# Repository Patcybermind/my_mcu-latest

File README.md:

# simple and cheap atmega 328 board
for simple projects where you dont need a usb port and just want the bare minimum

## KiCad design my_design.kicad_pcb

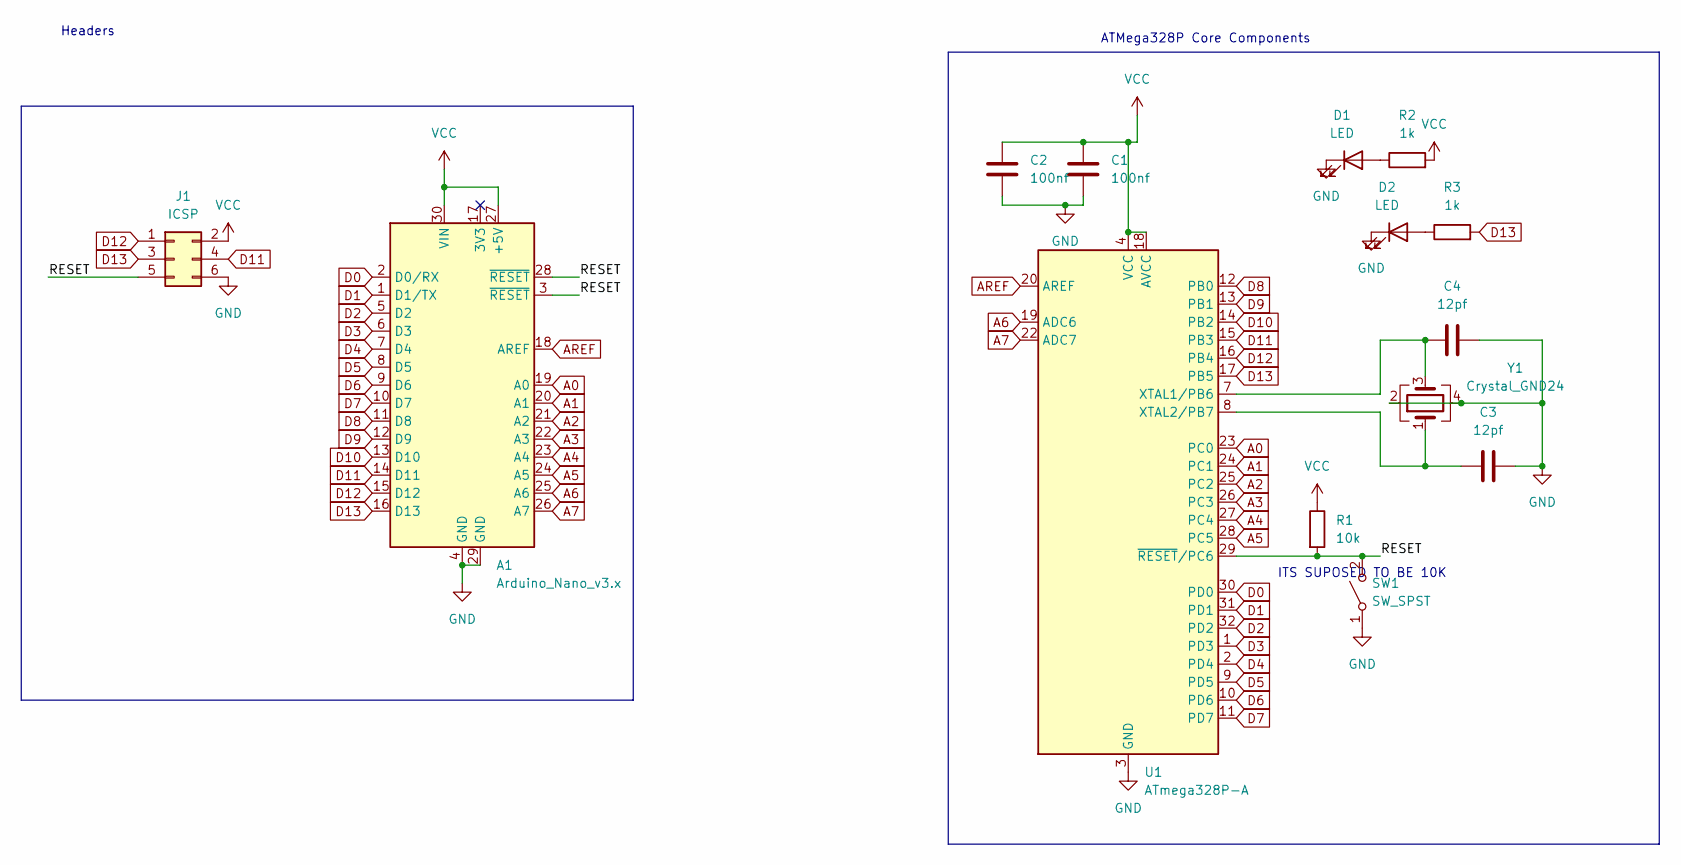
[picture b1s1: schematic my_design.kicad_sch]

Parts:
A1: Arduino_Nano_v3.x; Arduino_Nano_WithMountingHoles
C1, C2: 100nf; C_0805_2012Metric_Pad1.18x1.45mm_HandSolder; LCSC C49678
C3, C4: 12pf; C_0805_2012Metric_Pad1.18x1.45mm_HandSolder; LCSC C1792
D1, D2: LED; LED_0805_2012Metric_Pad1.15x1.40mm_HandSolder
J1: ICSP; PinHeader_2x03_P2.54mm_Vertical
R1: 10k; R_0805_2012Metric_Pad1.20x1.40mm_HandSolder; LCSC C17414
R2, R3: 1k; R_0805_2012Metric_Pad1.20x1.40mm_HandSolder
SW1: SW_SPST; SW_Push_1P1T_XKB_TS-1187A; LCSC C318884
U1: ATmega328P-A; TQFP-32_7x7mm_P0.8mm; LCSC C14877
Y1: Crystal_GND24; Crystal_SMD_3225-4Pin_3.2x2.5mm_HandSoldering; LCSC C13738

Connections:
/RESET: A1.3 (~RESET), A1.28 (~RESET), J1.5, R1.2, SW1.2 (B), U1.29 (~RESET/PC6)
A0: A1.19 (A0), U1.23 (PC0)
A1: A1.20 (A1), U1.24 (PC1)
A2: A1.21 (A2), U1.25 (PC2)
A3: A1.22 (A3), U1.26 (PC3)
A4: A1.23 (A4), U1.27 (PC4)
A5: A1.24 (A5), U1.28 (PC5)
A6: A1.25 (A6), U1.19 (ADC6)
A7: A1.26 (A7), U1.22 (ADC7)
AREF: A1.18 (AREF), U1.20 (AREF)
D0: A1.2 (D0/RX), U1.30 (PD0)
D1: A1.1 (D1/TX), U1.31 (PD1)
D2: A1.5 (D2), U1.32 (PD2)
D3: A1.6 (D3), U1.1 (PD3)
D4: A1.7 (D4), U1.2 (PD4)
D5: A1.8 (D5), U1.9 (PD5)
D6: A1.9 (D6), U1.10 (PD6)
D7: A1.10 (D7), U1.11 (PD7)
D8: A1.11 (D8), U1.12 (PB0)
D9: A1.12 (D9), U1.13 (PB1)
D10: A1.13 (D10), U1.14 (PB2)
D11: A1.14 (D11), J1.4, U1.15 (PB3)
D12: A1.15 (D12), J1.1, U1.16 (PB4)
D13: A1.16 (D13), J1.3, R3.2, U1.17 (PB5)
GND: A1.4 (GND), A1.29 (GND), C1.2, C2.1, C3.2, C4.2, D1.1 (K), D2.1 (K), J1.6, SW1.1 (A), U1.3 (GND), U1.5 (GND), U1.21 (GND), Y1.2, Y1.4
unnamed: D1.2 (A), R2.1
unnamed: D2.2 (A), R3.1
unnamed: C4.1, U1.7 (XTAL1/PB6), Y1.3
unnamed: C3.1, U1.8 (XTAL2/PB7), Y1.1
VCC: A1.27 (+5V), A1.30 (VIN), C1.1, C2.2, J1.2, R1.1, R2.2, U1.4 (VCC), U1.6 (VCC), U1.18 (AVCC)

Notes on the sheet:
ATMega328P Core Components
Headers
ITS SUPOSED TO BE 10K

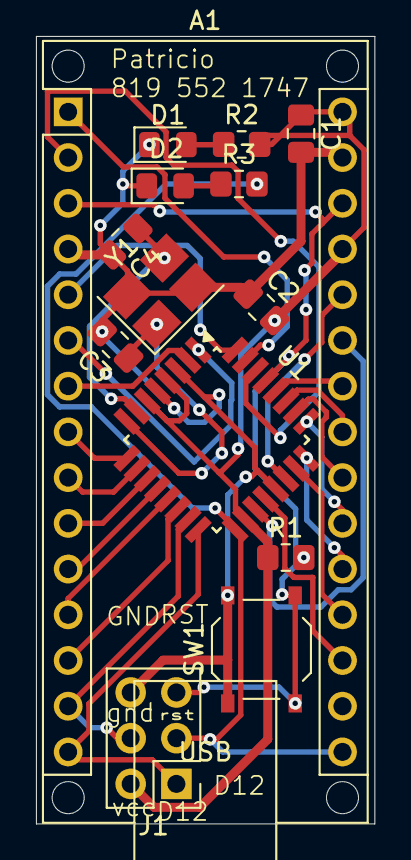
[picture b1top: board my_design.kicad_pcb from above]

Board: 2 copper layers, 18.8 x 43.8 mm, 14 parts (0 on the bottom side), 30 nets.

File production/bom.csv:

Designator,Footprint,Quantity,Value,LCSC Part #
A1,Arduino_Nano_WithMountingHoles,1,Arduino_Nano_v3.x,
"C1, C2",0805,2,100nf,C49678
"C3, C4",0805,2,12pf,C1792
"D1, D2",0805,2,LED,
J1,PinHeader_2x03_P2.54mm_Vertical,1,ICSP,
R1,0805,1,10k,C17414
"R2, R3",0805,2,1k,
SW1,SW_Push_1P1T_XKB_TS-1187A,1,SW_SPST,C318884
U1,TQFP-32_7x7mm_P0.8mm,1,ATmega328P-A,C14877
Y1,Crystal_SMD_3225-4Pin_3.2x2.5mm_HandSoldering,1,Crystal_GND24,C13738

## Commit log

2024-09-25 fiiststs
